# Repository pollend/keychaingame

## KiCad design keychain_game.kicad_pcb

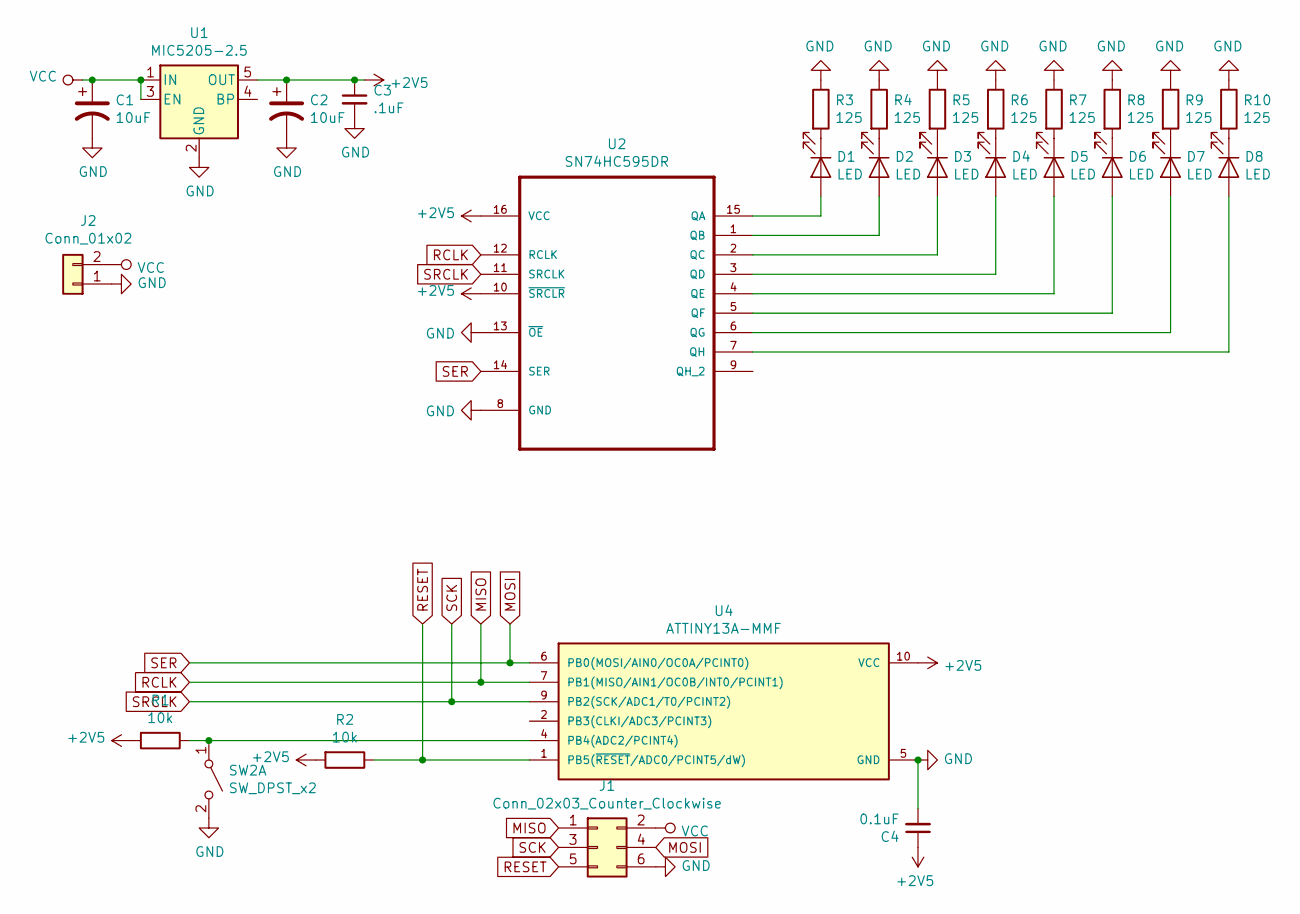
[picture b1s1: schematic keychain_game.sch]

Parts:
C1, C2: 10uF; CP_Tantalum_Case-B_EIA-3528-21_Reflow
C3: .1uF; C_0603_1608Metric
C4: 0.1uF; C_0603_1608Metric
D1, D2, D3, D4, D5, D6, D7, D8: LED; LED_0603_1608Metric
J1: Conn_02x03_Counter_Clockwise; PinHeader_2x03_P2.54mm_Vertical
J2: Conn_01x02; Keystone_3034_1x20mm-CoinCell
R1, R2: 10k; R_0805_2012Metric
R3, R4, R5, R6, R7, R8, R9, R10: 125; R_0805_2012Metric
SW2: SW_DPST_x2; SW_SPST_B3U-1000P
U1: MIC5205-2.5; SOT-23-5
U2: SN74HC595DR; SOIC-16W_5.3x10.2mm_P1.27mm
U4: ATTINY13A-MMF; DFN-10-1EP_3x3mm_P0.5mm_EP1.55x2.48mm

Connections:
+2V5: C2.1, C3.1, C4.1, R1.2, R2.2, U1.5 (OUT), U2.10 (~SRCLR), U2.16 (VCC), U4.10 (VCC)
GND: C1.2, C2.2, C3.2, C4.2, J1.6, J2.1, R3.1, R4.1, R5.1, R6.1, R7.1, R8.1, R9.1, R10.1, SW2.2 (B), U1.2 (GND), U2.8 (GND), U2.13 (~OE), U4.5 (GND)
MISO: J1.1, U2.12 (RCLK), U4.7 (PB1(MISO/AIN1/OC0B/INT0/PCINT1))
MOSI: J1.4, U2.14 (SER), U4.6 (PB0(MOSI/AIN0/OC0A/PCINT0))
unnamed: D1.1 (K), R3.2
unnamed: D1.2 (A), U2.15 (QA)
unnamed: D2.1 (K), R4.2
unnamed: D2.2 (A), U2.1 (QB)
unnamed: D3.1 (K), R5.2
unnamed: D3.2 (A), U2.2 (QC)
unnamed: D4.1 (K), R6.2
unnamed: D4.2 (A), U2.3 (QD)
unnamed: D5.1 (K), R7.2
unnamed: D5.2 (A), U2.4 (QE)
unnamed: D6.1 (K), R8.2
unnamed: D6.2 (A), U2.5 (QF)
unnamed: D7.1 (K), R9.2
unnamed: D7.2 (A), U2.6 (QG)
unnamed: D8.1 (K), R10.2
unnamed: D8.2 (A), U2.7 (QH)
unnamed: R1.1, SW2.1 (A), U4.4 (PB4(ADC2/PCINT4))
RESET: J1.5, R2.1, U4.1 (PB5(~RESET~/ADC0/PCINT5/dW))
SCK: J1.3, U2.11 (SRCLK), U4.9 (PB2(SCK/ADC1/T0/PCINT2))
VCC: C1.1, J1.2, J2.2, U1.1 (IN), U1.3 (EN)

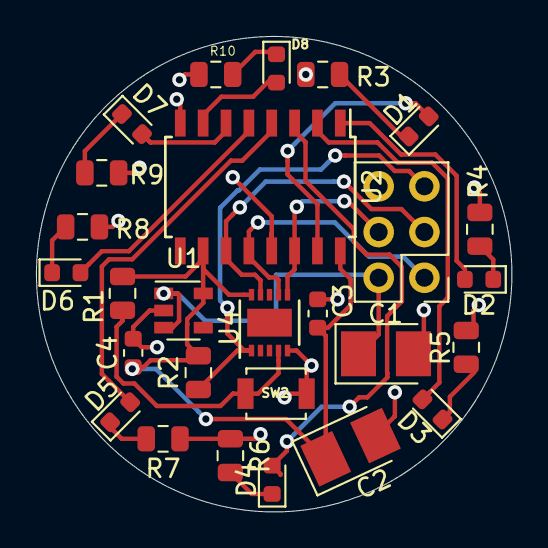
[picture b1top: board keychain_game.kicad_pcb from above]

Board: 2 copper layers, 26.4 x 26.4 mm, 28 parts (1 on the bottom side), 24 nets.

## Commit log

2018-08-23 start
2018-08-31 updated schematic
2018-08-31 started working on keychain
2018-09-01 finished board
2018-09-01 updated ground plane
2018-09-01 shifted edge cut
2018-09-10 updated desgin slightly
